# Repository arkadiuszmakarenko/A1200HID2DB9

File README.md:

# A1200HID2DB9 - Work in progress
4 Layer PCB Board for ReAmiga1200 and firmware for CH32V203C

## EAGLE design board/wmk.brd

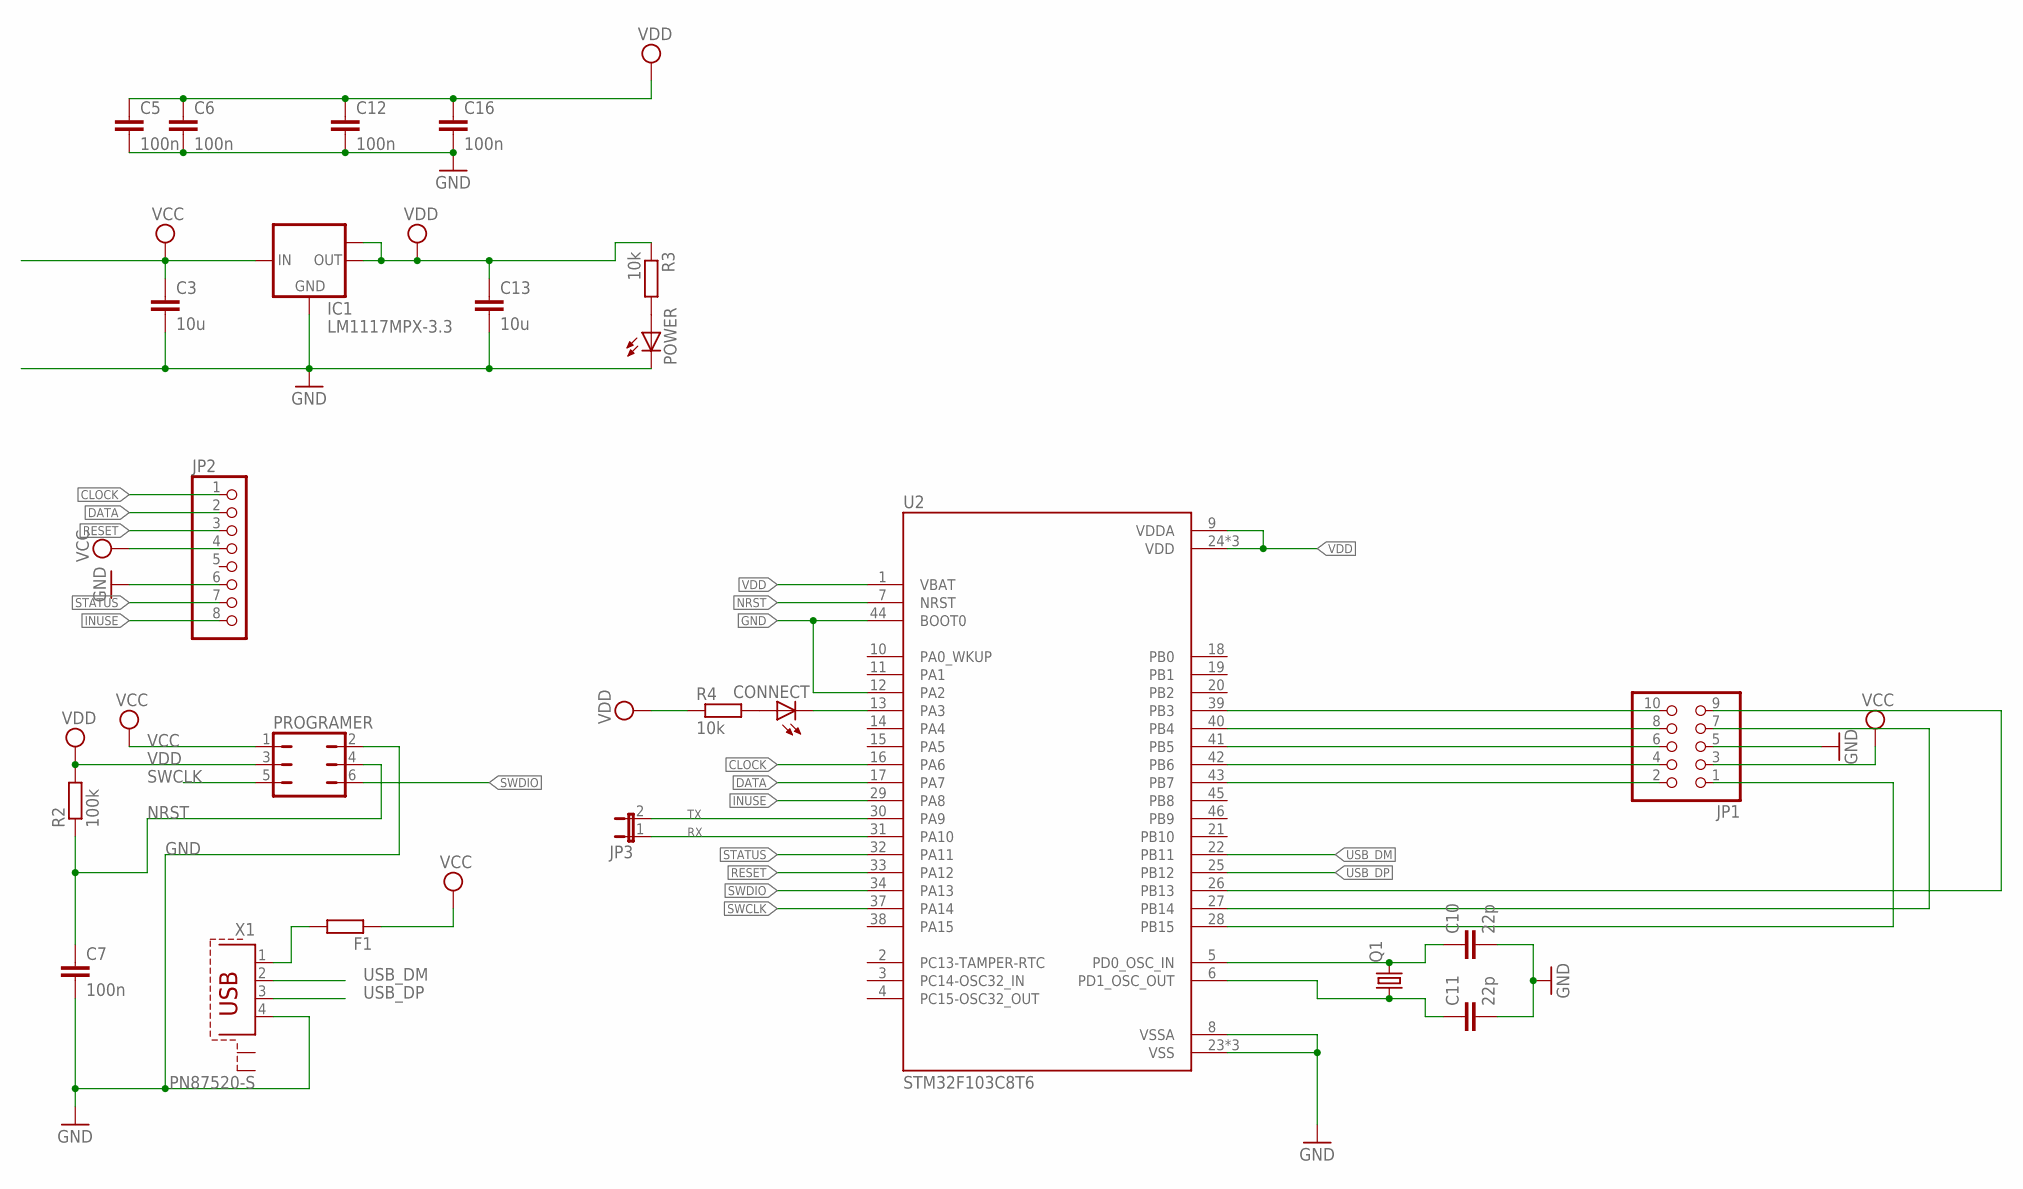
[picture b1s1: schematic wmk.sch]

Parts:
C3, C13: 10u; C1206
C5, C6, C7, C12, C16: 100n; C0603
C10, C11: 22p; C0603
CONNECT: LEDSML0805; SML0805
F1: RR1206; R1206
IC1: LM1117MPX-3.3; SOT223
JP1: PINHD-2X5; 2X05
JP2: PINHD-1X8; 1X08
JP3: JP1E; JP1
POWER: LEDSML0805; SML0805
PROGRAMER: JP3Q
Q1: CRYSTALHC49S; HC49/S
R2: 100k; R0603
R3, R4: 10k; R0603
U2: STM32F103C8T6; QFP50P900X900X160-48N
X1: PN87520-S

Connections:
CLOCK: JP2.1, U2.16 (PA6)
DATA: JP2.2, U2.17 (PA7)
GND: C3.2, C5.2, C6.2, C7.2, C10.2, C11.2, C12.2, C13.2, C16.2, IC1.1 (GND), JP1.5, JP2.6, POWER.C, PROGRAMER.2, U2.8 (VSSA), U2.12 (PA2), U2.23 (VSS), U2.35 (VSS), U2.44 (BOOT0), U2.47 (VSS), X1.4
INUSE: JP2.8, U2.29 (PA8)
unnamed: C10.1, Q1.2, U2.5 (PD0_OSC_IN)
unnamed: C11.1, Q1.1, U2.6 (PD1_OSC_OUT)
unnamed: CONNECT.C, U2.13 (PA3)
unnamed: F1.2, X1.1
unnamed: JP1.10, U2.39 (PB3)
unnamed: CONNECT.A, R4.2
unnamed: JP1.8, U2.40 (PB4)
unnamed: JP1.6, U2.41 (PB5)
unnamed: JP1.4, U2.42 (PB6)
unnamed: JP1.2, U2.43 (PB7)
unnamed: POWER.A, R3.2
unnamed: JP1.7, U2.27 (PB14)
unnamed: JP1.9, U2.26 (PB13)
unnamed: JP1.1, U2.28 (PB15)
NRST: C7.1, PROGRAMER.4, R2.1, U2.7 (NRST)
RESET: JP2.3, U2.33 (PA12)
RX: JP3.1, U2.31 (PA10)
STATUS: JP2.7, U2.32 (PA11)
SWCLK: PROGRAMER.5, U2.37 (PA14)
SWDIO: PROGRAMER.6, U2.34 (PA13)
TX: JP3.2, U2.30 (PA9)
USB_DM: U2.22 (PB11), X1.2
USB_DP: U2.25 (PB12), X1.3
VCC: C3.1, F1.1, IC1.3 (IN), JP1.3, JP2.4, PROGRAMER.1
VDD: C5.1, C6.1, C12.1, C13.1, C16.1, IC1.2 (OUT), IC1.TAB (OUT1), PROGRAMER.3, R2.2, R3.1, R4.1, U2.1 (VBAT), U2.9 (VDDA), U2.24 (VDD), U2.36 (VDD), U2.48 (VDD)

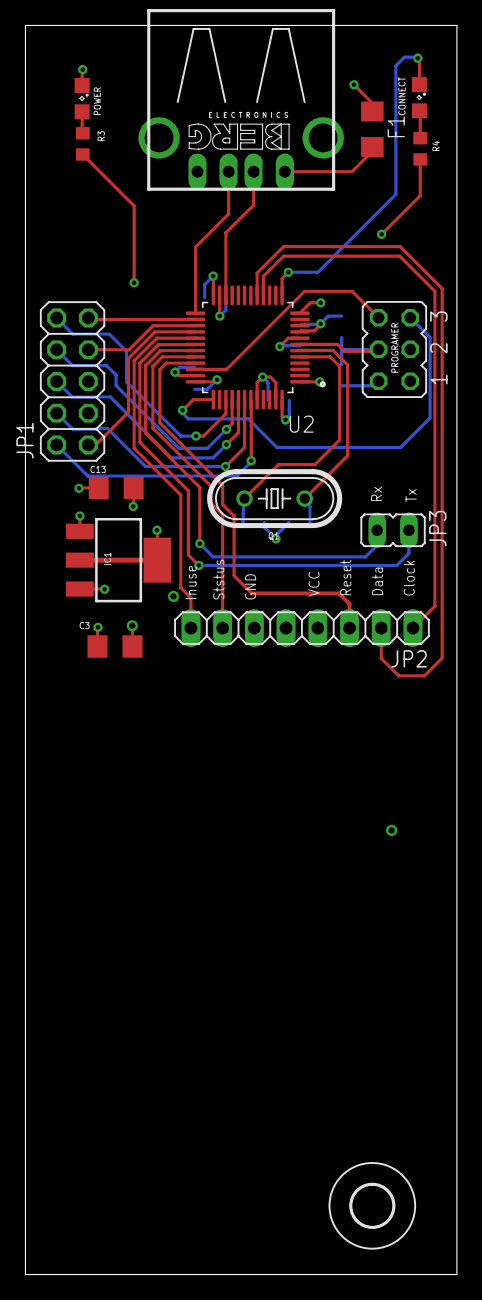
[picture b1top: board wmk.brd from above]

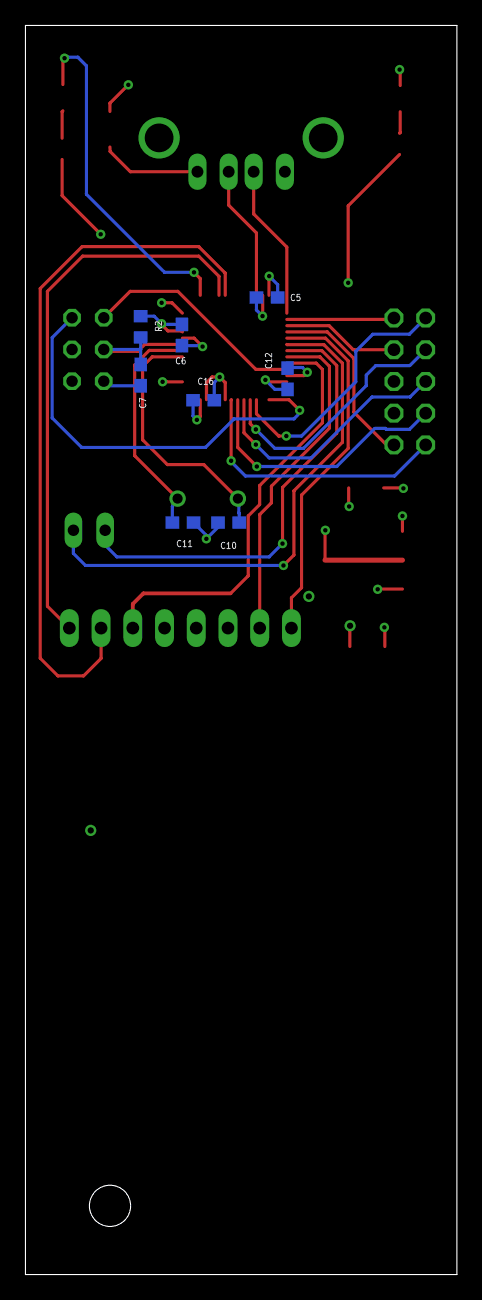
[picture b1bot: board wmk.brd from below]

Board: 4 copper layers, 34.5 x 100.0 mm, 24 parts (8 on the bottom side), 29 nets.

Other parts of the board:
U$1: 3,3

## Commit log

2022-01-08 Initial commit
    Initial commit with basic working setup
2022-09-08 https://github.com/kulamario/Amiga-Mouse-Usb-DB9
2022-12-11 Firmware for new board marked as 27/08/2022
2022-12-18 Dropping dependency on stm32cubeide, new makefile.
2022-12-21 delay us, tim4 config, utils and keyboard class
2023-01-07 Hub Support initial work
2023-01-08 Class Request Ready plus few control requests
2023-01-10 First basic refactoring
2023-01-13 Progress on handling port state, interfaces etc.
2023-01-18 Connection, disconnection, enumeration handled.
2023-01-21 Data received from devices from multiple ports
2023-01-22 Jumping between ports sorted
2023-01-23 Fixing issues with pipe allocation, and tidy up.
2023-01-24 HUB mouse and keyboard init + tidy up
2023-01-29 bugfixing+mouse, keyboard and gamepad support
2023-01-29 Hub enum tidy up
2023-01-30 Keyboard hub select, and some debugging
2023-02-01 Util Device selector
2023-02-04 Send all keypresses at once (no 5ms gap)
2023-02-07 Mouse,Keybd,Gamepad work
2023-06-04 First pass of the CH32 proto. unchecked and untested.
2023-06-10 Added TX/RX and moved LEDS
2024-02-29 4Layer KiCad PCB, CH32V203C project
2024-03-12 V203C firmware port
2024-03-12 Reset fix
2024-03-15 bugfix wheel configuration
